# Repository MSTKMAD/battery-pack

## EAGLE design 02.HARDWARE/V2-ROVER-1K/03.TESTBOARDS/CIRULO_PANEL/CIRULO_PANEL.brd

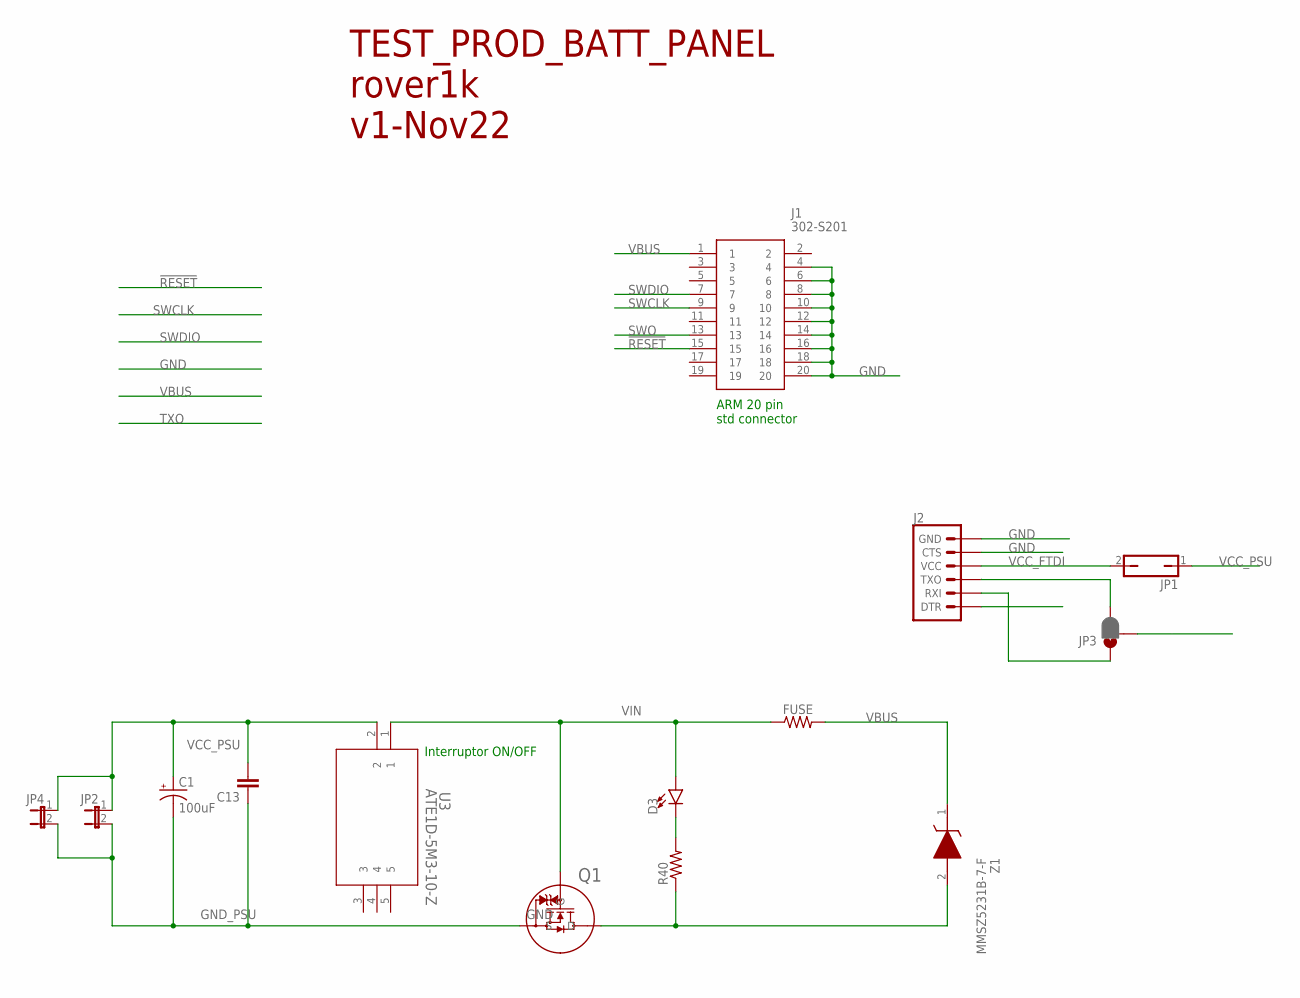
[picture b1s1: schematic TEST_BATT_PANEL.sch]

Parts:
C1: 100uF; CPOL-RADIAL-2.5MM-6.5MM
C13: C-EUC0805; C0805
D3: LED3MM; LED_3MM
FUSE: 0805
J1: 302-S201; SHDR20W66P254_2X10_3300X905X90
J2: 6_PIN_SERIAL_TARGET; 1X06
JP1: JP1Q; JP1
JP2, JP4: JP1E; JP1
JP3: JUMPER-SMT_3_1-NC_PASTE_NO-SILK; SMT-JUMPER_3_1-NC_PASTE_NO-SILK
Q1: PJA3416AE_R1_00001; SOT23_PJA3416_PNJ
R40: 10K; 0805
U3: ATE1D-5M3-10-Z; SPDT05_ATE1D_9P5X8_NDC
Z1: MMSZ5231B-7-F; SOD3716X145N

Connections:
!RESET: J1.15
GND: J1.4, J1.6, J1.8, J1.10, J1.12, J1.14, J1.16, J1.18, J1.20, J2.5 (CTS), J2.6 (GND), Q1.3 (D), R40.1, Z1.2 (A)
GND_PSU: C1.2 (-), C13.1, JP2.2, JP4.2, Q1.2 (S)
unnamed: D3.K (C), R40.2
RXI: J2.3 (TXO), JP3.3
SWCLK: J1.9
SWDIO: J1.7
SWO: J1.13
TXO: J2.2 (RXI), JP3.1
VBUS: FUSE.2, J1.1, Z1.1 (K)
VCC_FTDI: J2.4 (VCC), JP1.2
VCC_PSU: C1.1 (+), C13.2, JP1.1, JP2.1, JP4.1, U3.2
VIN: D3.A, FUSE.1, Q1.1 (G), U3.1

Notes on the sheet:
TEST_PROD_BATT_PANEL rover1k v1-Nov22
ARM 20 pin std connector
Interruptor ON/OFF

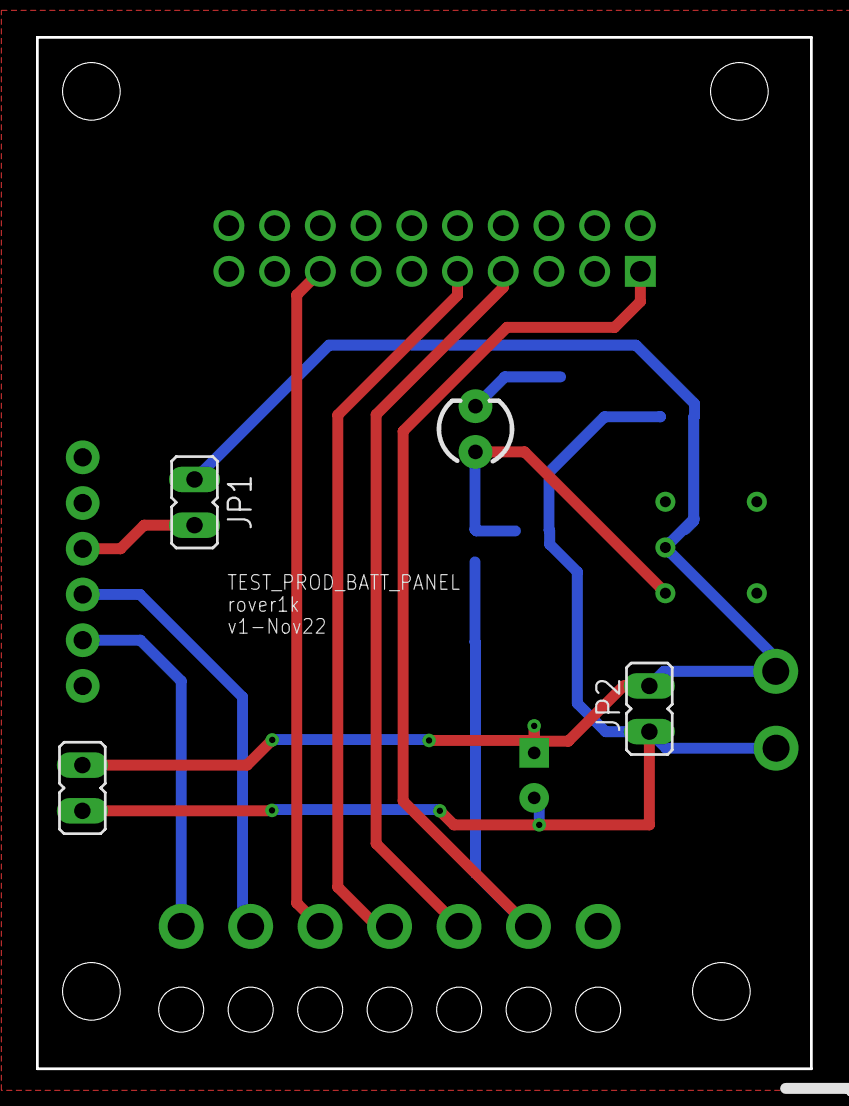
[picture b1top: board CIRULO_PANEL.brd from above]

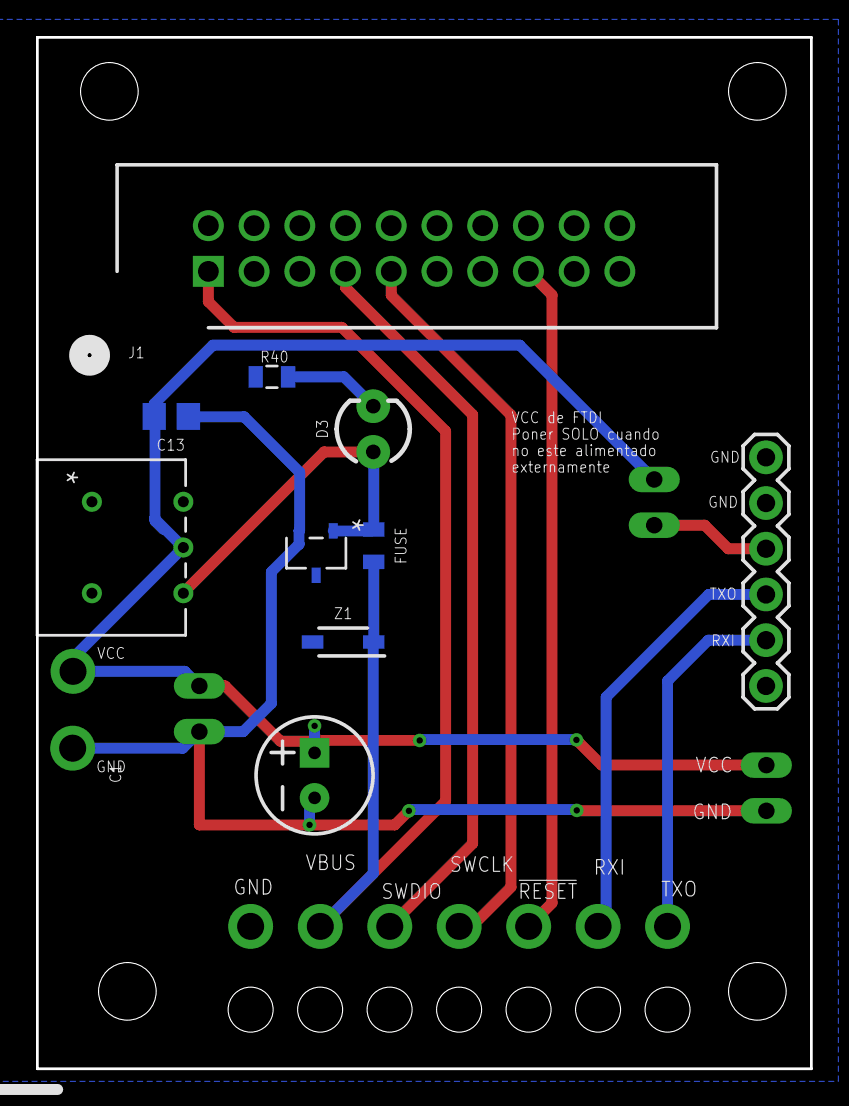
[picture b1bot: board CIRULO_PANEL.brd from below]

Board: 2 copper layers, 43.0 x 57.3 mm, 13 parts (10 on the bottom side), 7 nets.

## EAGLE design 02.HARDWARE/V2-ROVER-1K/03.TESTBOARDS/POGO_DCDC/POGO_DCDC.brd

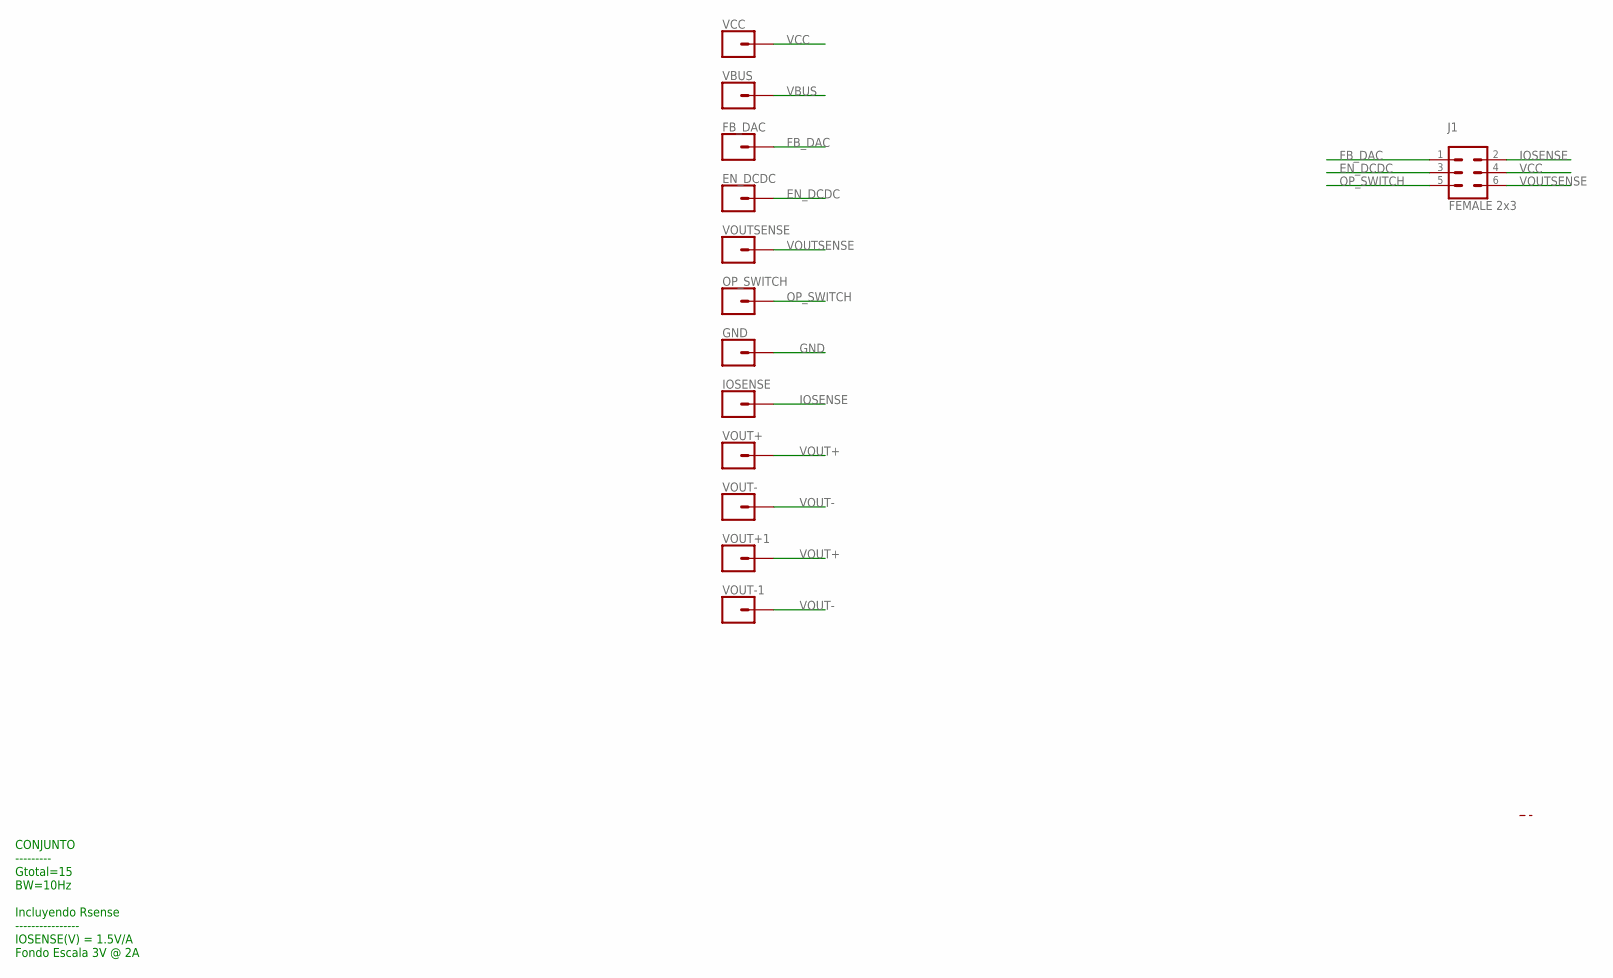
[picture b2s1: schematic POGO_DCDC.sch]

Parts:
EN_DCDC: CONN_01POGOPIN_HOLE_LARGE; 1X01_POGOPIN_HOLE_0.061_DIA
FB_DAC: CONN_01POGOPIN_HOLE_LARGE; 1X01_POGOPIN_HOLE_0.061_DIA
GND: CONN_01POGOPIN_HOLE_LARGE; 1X01_POGOPIN_HOLE_0.061_DIA
IOSENSE: CONN_01POGOPIN_HOLE_LARGE; 1X01_POGOPIN_HOLE_0.061_DIA
J1: FEMALE 2x3; 2X3
OP_SWITCH: CONN_01POGOPIN_HOLE_LARGE; 1X01_POGOPIN_HOLE_0.061_DIA
VBUS: CONN_01POGOPIN_HOLE_LARGE; 1X01_POGOPIN_HOLE_0.061_DIA
VCC: CONN_01POGOPIN_HOLE_LARGE; 1X01_POGOPIN_HOLE_0.061_DIA
VOUT+, VOUT+1: CONN_01POGOPIN_HOLE_LARGE; 1X01_POGOPIN_HOLE_0.061_DIA
VOUT-, VOUT-1: CONN_01POGOPIN_HOLE_LARGE; 1X01_POGOPIN_HOLE_0.061_DIA
VOUTSENSE: CONN_01POGOPIN_HOLE_LARGE; 1X01_POGOPIN_HOLE_0.061_DIA

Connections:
EN_DCDC: EN_DCDC.2, J1.3
FB_DAC: FB_DAC.2, J1.1
GND: GND.2
IOSENSE: IOSENSE.2, J1.2
OP_SWITCH: J1.5, OP_SWITCH.2
VBUS: VBUS.2
VCC: J1.4, VCC.2
VOUT+: VOUT+.2, VOUT+1.2
VOUT-: VOUT-.2, VOUT-1.2
VOUTSENSE: J1.6, VOUTSENSE.2

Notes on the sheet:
CONJUNTO --------- Gtotal=15 BW=10Hz Incluyendo Rsense ---------------- IOSENSE(V) = 1.5V/A Fondo Escala 3V @ 2A

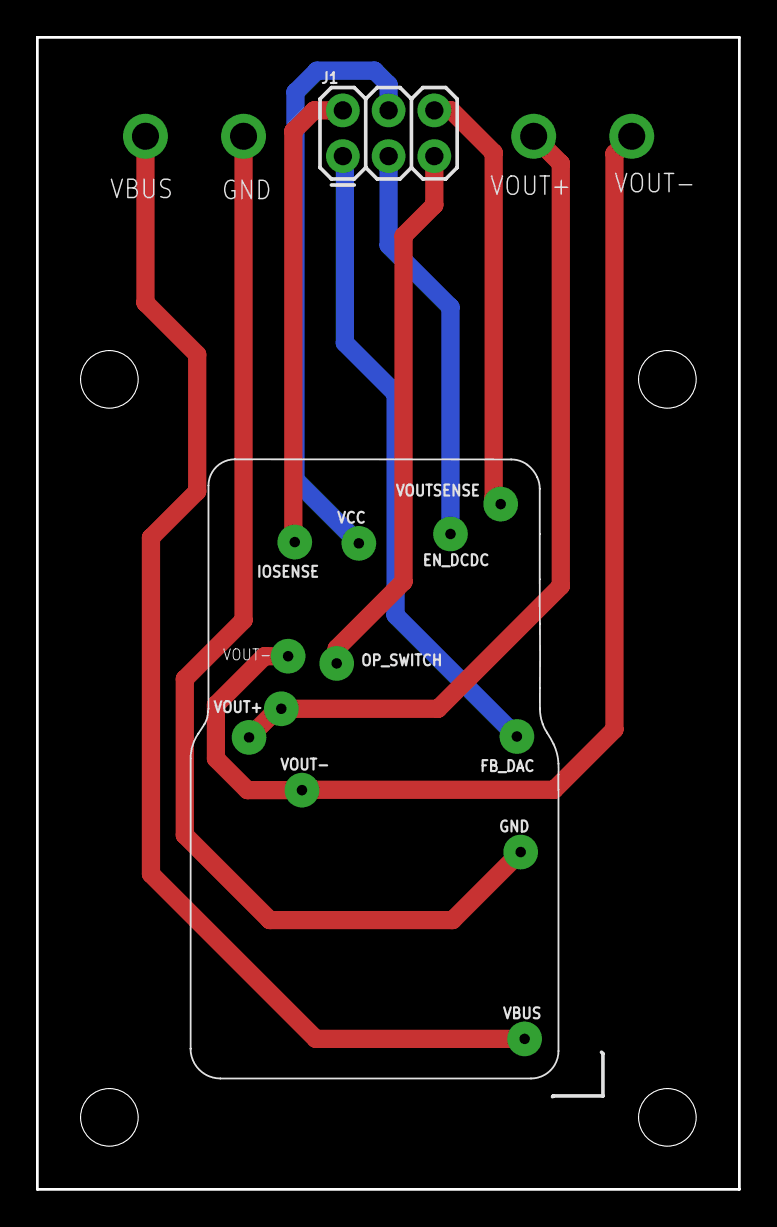
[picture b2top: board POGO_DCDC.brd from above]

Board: 2 copper layers, 39.0 x 64.0 mm, 13 parts (0 on the bottom side), 8 nets.

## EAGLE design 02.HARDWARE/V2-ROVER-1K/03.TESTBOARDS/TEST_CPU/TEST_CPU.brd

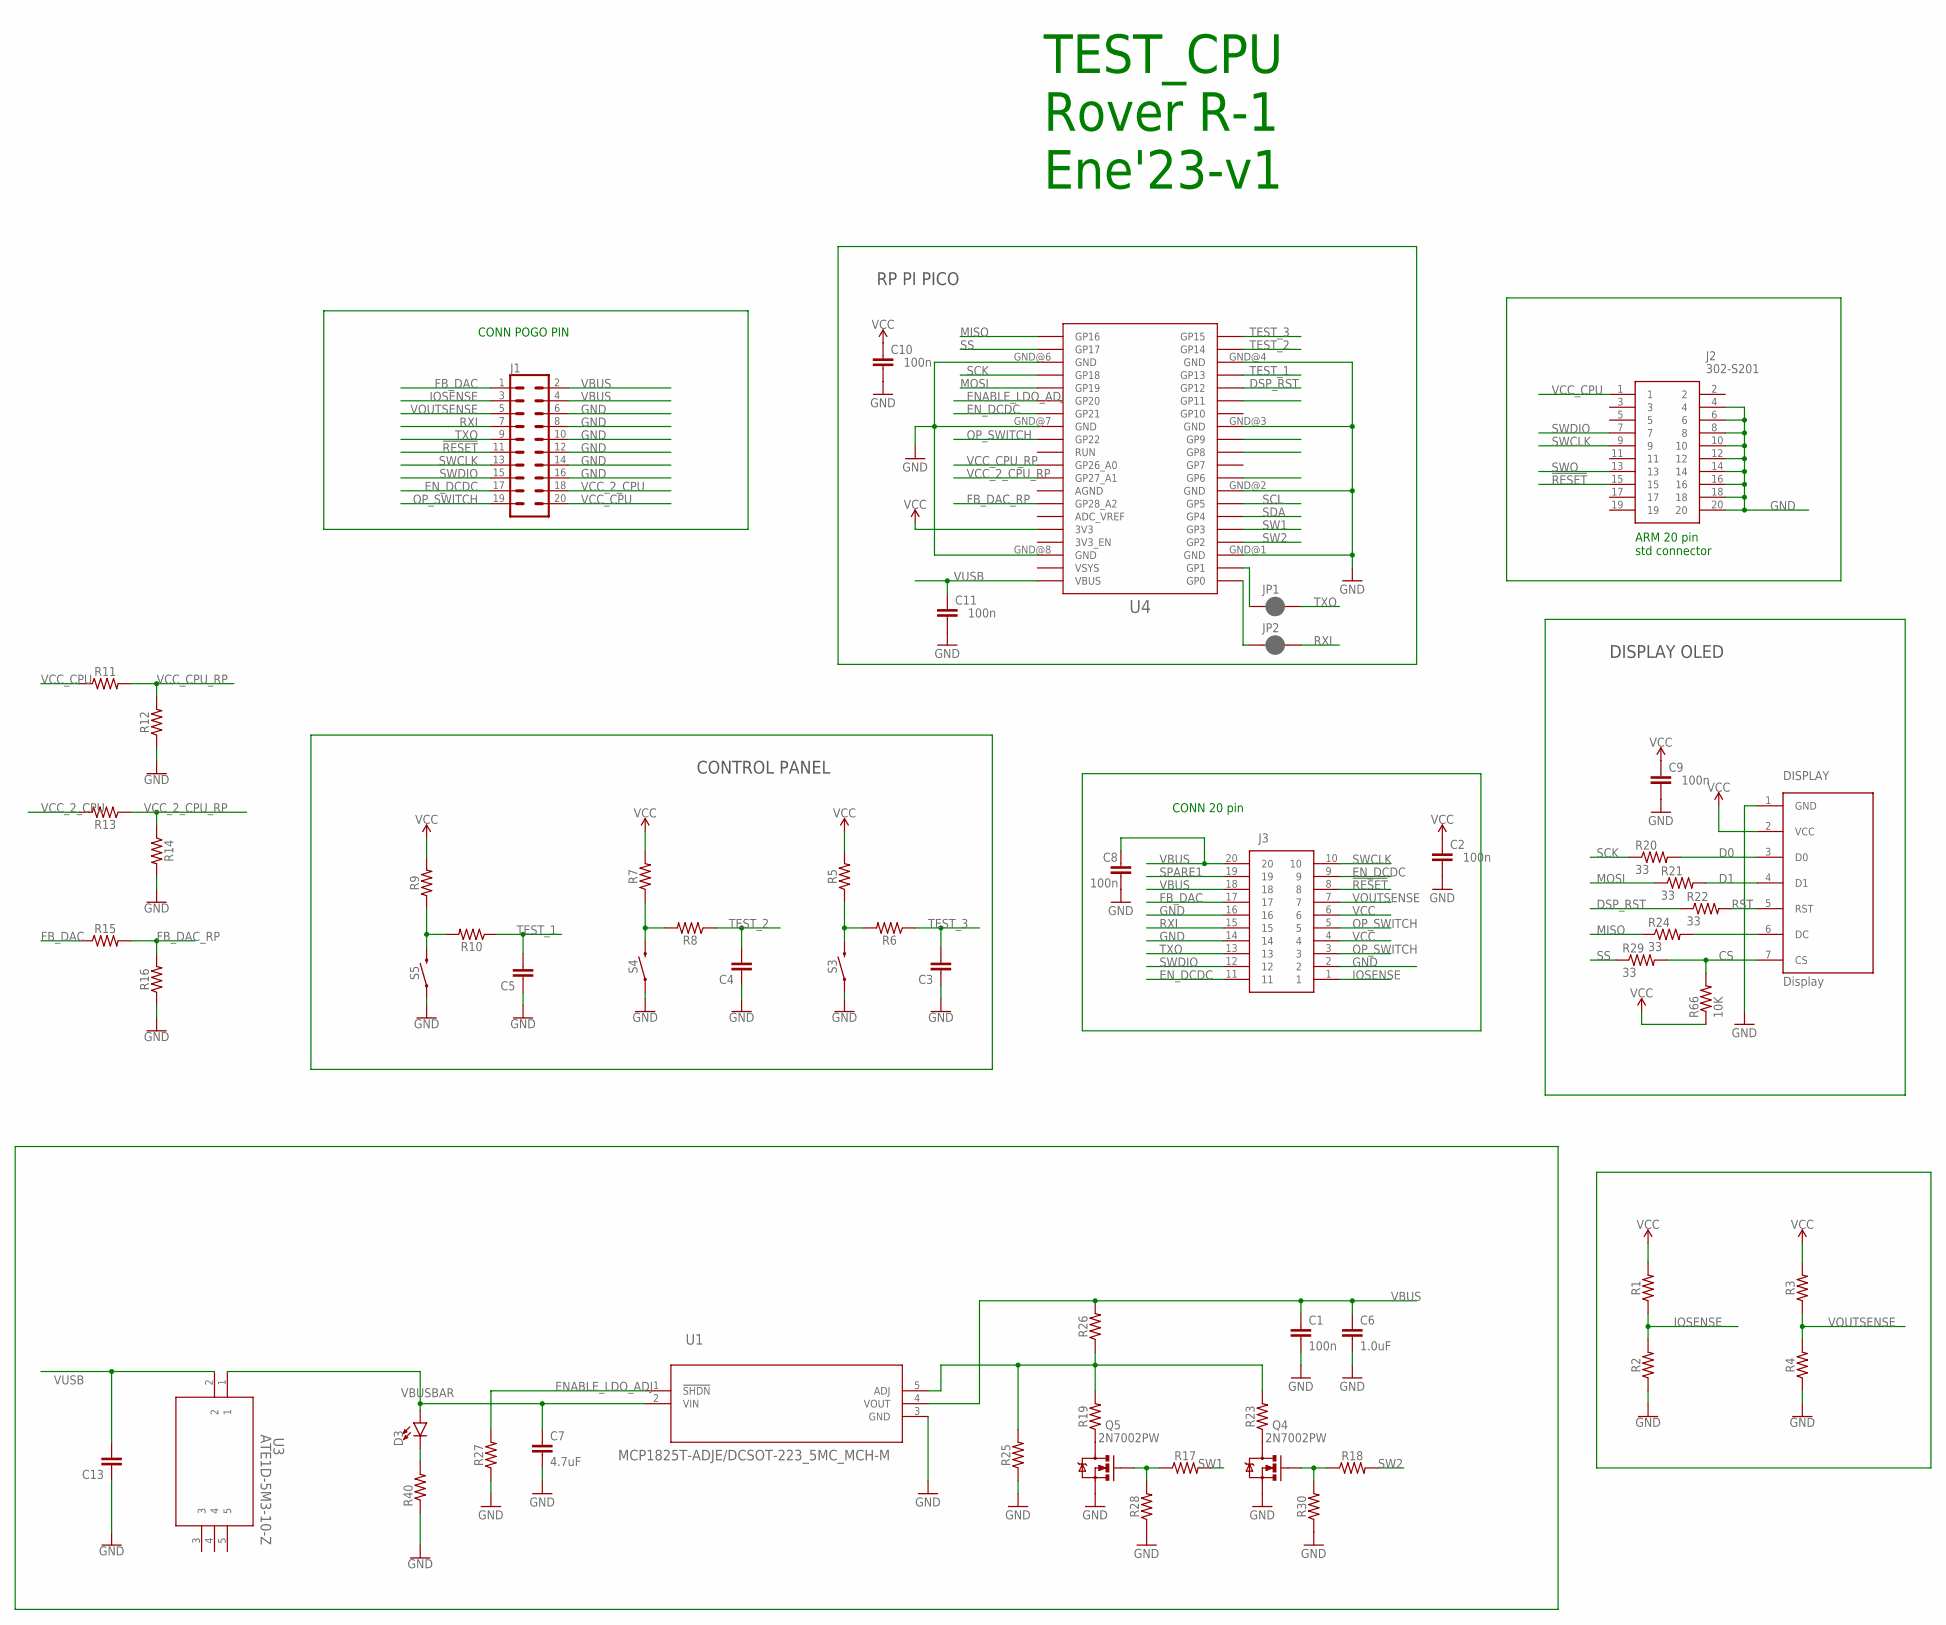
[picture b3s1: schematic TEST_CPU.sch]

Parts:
C1, C2, C8, C9, C10, C11: 100n; 0805
C3, C4, C5, C13: C-EUC0805; C0805
C6: 1.0uF; 0805
C7: 4.7uF; 0603
D3: LED3MM; LED_3MM
DISPLAY: Display; OLED_LCD
J1: CONN_10X2; 2X10
J2: 302-S201; SHDR20W66P254_2X10_3300X905X90
J3: DF40C-20DP-0.4V_51_; DF40C-20DPA
JP1, JP2: JUMPER-SMT_2_NC_PASTE_SILK; SMT-JUMPER_2_NC_PASTE_SILK
Q4, Q5: 2N7002PW; SOT323
R1, R2, R3, R4, R5, R6, R7, R8, R9, R10, R11, R12, R13, R14, R15, R16, R17, R18, R19, R23, R25, R26, R27, R28, R30: 0805
R20, R21, R22, R24, R29: 33; 0805
R40, R66: 10K; 0805
S3, S4, S5: MOMENTARY-SWITCH-SPST-SMD-5.2MM; TACTILE_SWITCH_SMD_5.2MM
U1: MCP1825T-ADJE/DCSOT-223_5MC_MCH-M; SOT-223_5MC_MCH-M
U3: ATE1D-5M3-10-Z; SPDT05_ATE1D_9P5X8_NDC
U4: RPI_PICO_IG-TH; RPI_PICO_TH

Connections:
!RESET: J1.11, J2.15, J3.8
CS: DISPLAY.7 (CS), R29.2, R66.2
D0: DISPLAY.3 (D0), R20.2
D1: DISPLAY.4 (D1), R21.2
DSP_RST: R22.1, U4.GP12
ENABLE_LDO_ADJ: R27.2, U1.1 (!SHDN), U4.GP20
EN_DCDC: J1.17, J3.9, J3.11, U4.GP21
FB_DAC: J1.1, J3.17, R15.1
FB_DAC_RP: R15.2, R16.2, U4.GP28_A2
GND: C1.2, C2.2, C3.1, C4.1, C5.1, C6.2, C7.2, C8.2, C9.2, C10.2, C11.2, C13.1, DISPLAY.1 (GND), J1.6, J1.8, J1.10, J1.12, J1.14, J1.16, J2.4, J2.6, J2.8, J2.10, J2.12, J2.14, J2.16, J2.18, J2.20, J3.2, J3.14, J3.16, Q4.2 (S), Q5.2 (S), R2.1, R4.1, R12.1, R14.2, R16.1, R25.1, R27.1, R28.1, R30.1, R40.1, S3.1, S4.1, S5.1, U1.3 (GND), U4.GND@1 (GND), U4.GND@2 (GND), U4.GND@3 (GND), U4.GND@4 (GND), U4.GND@6 (GND), U4.GND@7 (GND), U4.GND@8 (GND)
IOSENSE: J1.3, J3.1, R1.1, R2.2
MISO: R24.1, U4.GP16
MOSI: R21.1, U4.GP19
unnamed: R5.1, R6.2, S3.3 (2)
unnamed: R7.1, R8.2, S4.3 (2)
unnamed: JP1.1, U4.GP1
unnamed: R9.1, R10.2, S5.3 (2)
unnamed: JP2.1, U4.GP0
unnamed: DISPLAY.6 (DC), R24.2
unnamed: R19.2, R23.2, R25.2, R26.1, U1.5 (ADJ)
unnamed: Q5.1 (G), R17.1, R28.2
unnamed: D3.K (C), R40.2
unnamed: Q5.3 (D), R19.1
unnamed: Q4.1 (G), R18.1, R30.2
unnamed: Q4.3 (D), R23.1
OP_SWITCH: J1.19, J3.3, J3.5, U4.GP22
RST: DISPLAY.5 (RST), R22.2
RXI: J1.7, J3.15, JP2.2
SCK: R20.1, U4.GP18
SCL: U4.GP5
SDA: U4.GP4
SPARE1: J3.19
SS: R29.1, U4.GP17
SW1: R17.2, U4.GP3
SW2: R18.2, U4.GP2
SWCLK: J1.13, J2.9, J3.10
SWDIO: J1.15, J2.7, J3.12
SWO: J2.13
TEST_1: C5.2, R10.1, U4.GP13
TEST_2: C4.2, R8.1, U4.GP14
TEST_3: C3.2, R6.1, U4.GP15
TXO: J1.9, J3.13, JP1.2
VBUS: C1.1, C6.1, C8.1, J1.2, J1.4, J3.18, J3.20, R26.2, U1.4 (VOUT)
VBUSBAR: C7.1, D3.A, U1.2 (VIN), U3.1
VCC: C2.1, C9.1, C10.1, DISPLAY.2 (VCC), J3.4, J3.6, R1.2, R3.2, R5.2, R7.2, R9.2, R66.1, U4.3V3
VCC_2_CPU: J1.18, R13.2
VCC_2_CPU_RP: R13.1, R14.1, U4.GP27_A1
VCC_CPU: J1.20, J2.1, R11.1
VCC_CPU_RP: R11.2, R12.2, U4.GP26_A0
VOUTSENSE: J1.5, J3.7, R3.1, R4.2
VUSB: C11.1, C13.2, U3.2, U4.VBUS

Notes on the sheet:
TEST_CPU Rover R-1 Ene'23-v1
CONTROL PANEL
DISPLAY OLED
RP PI PICO
ARM 20 pin std connector
CONN 20 pin
CONN POGO PIN

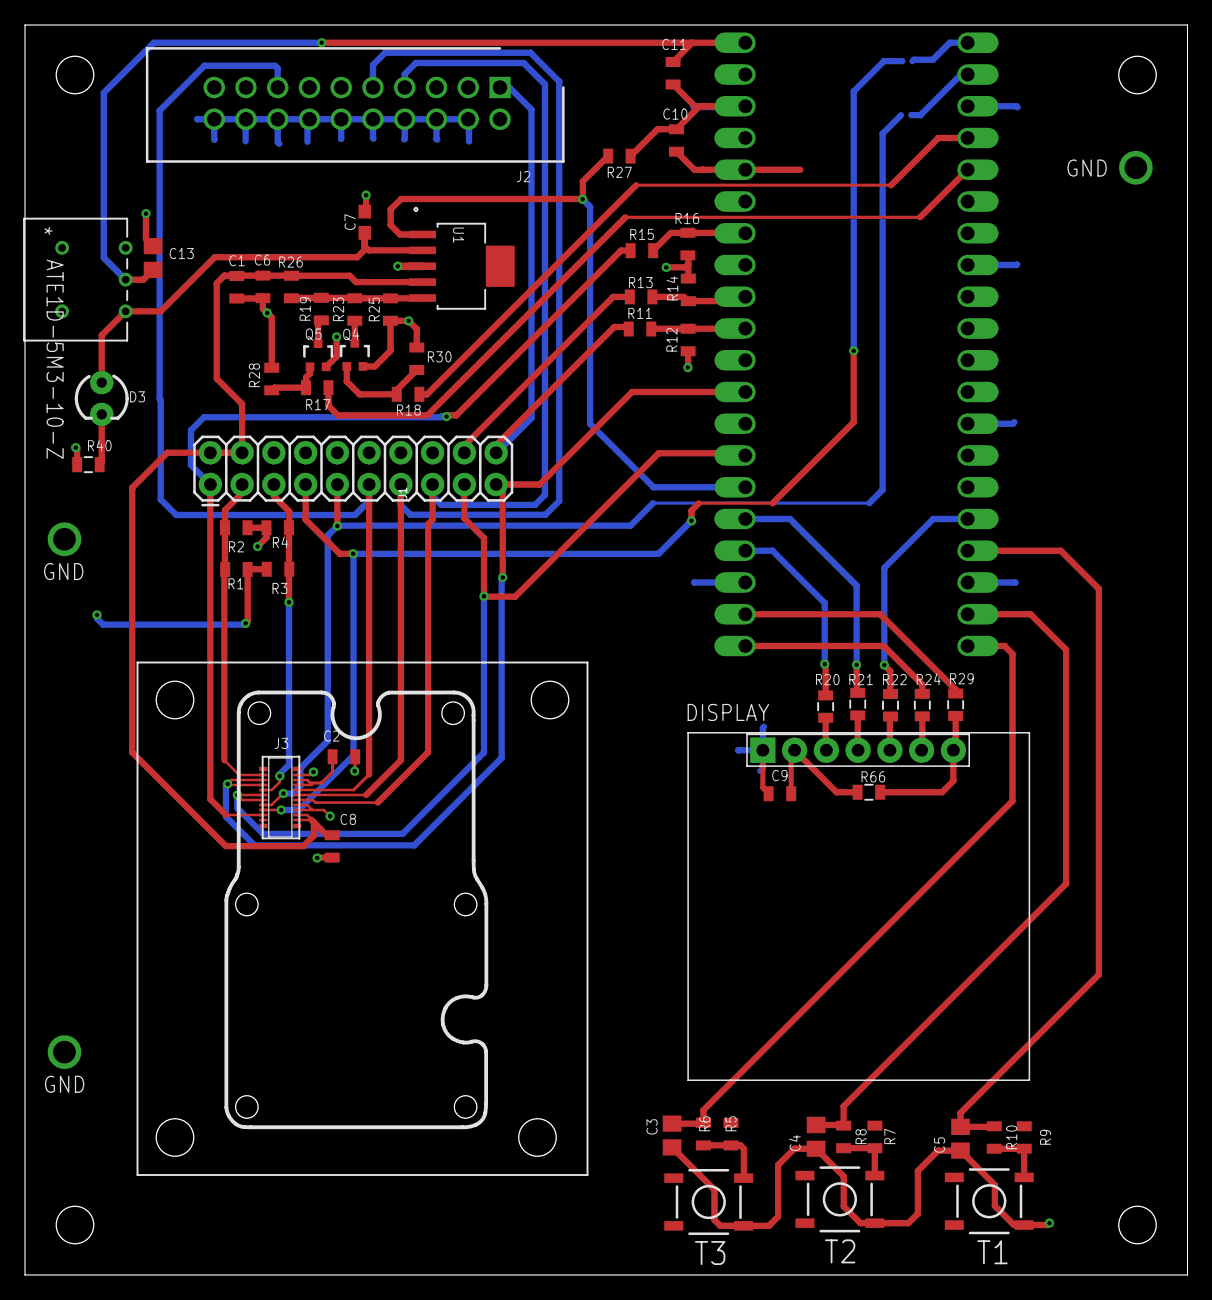
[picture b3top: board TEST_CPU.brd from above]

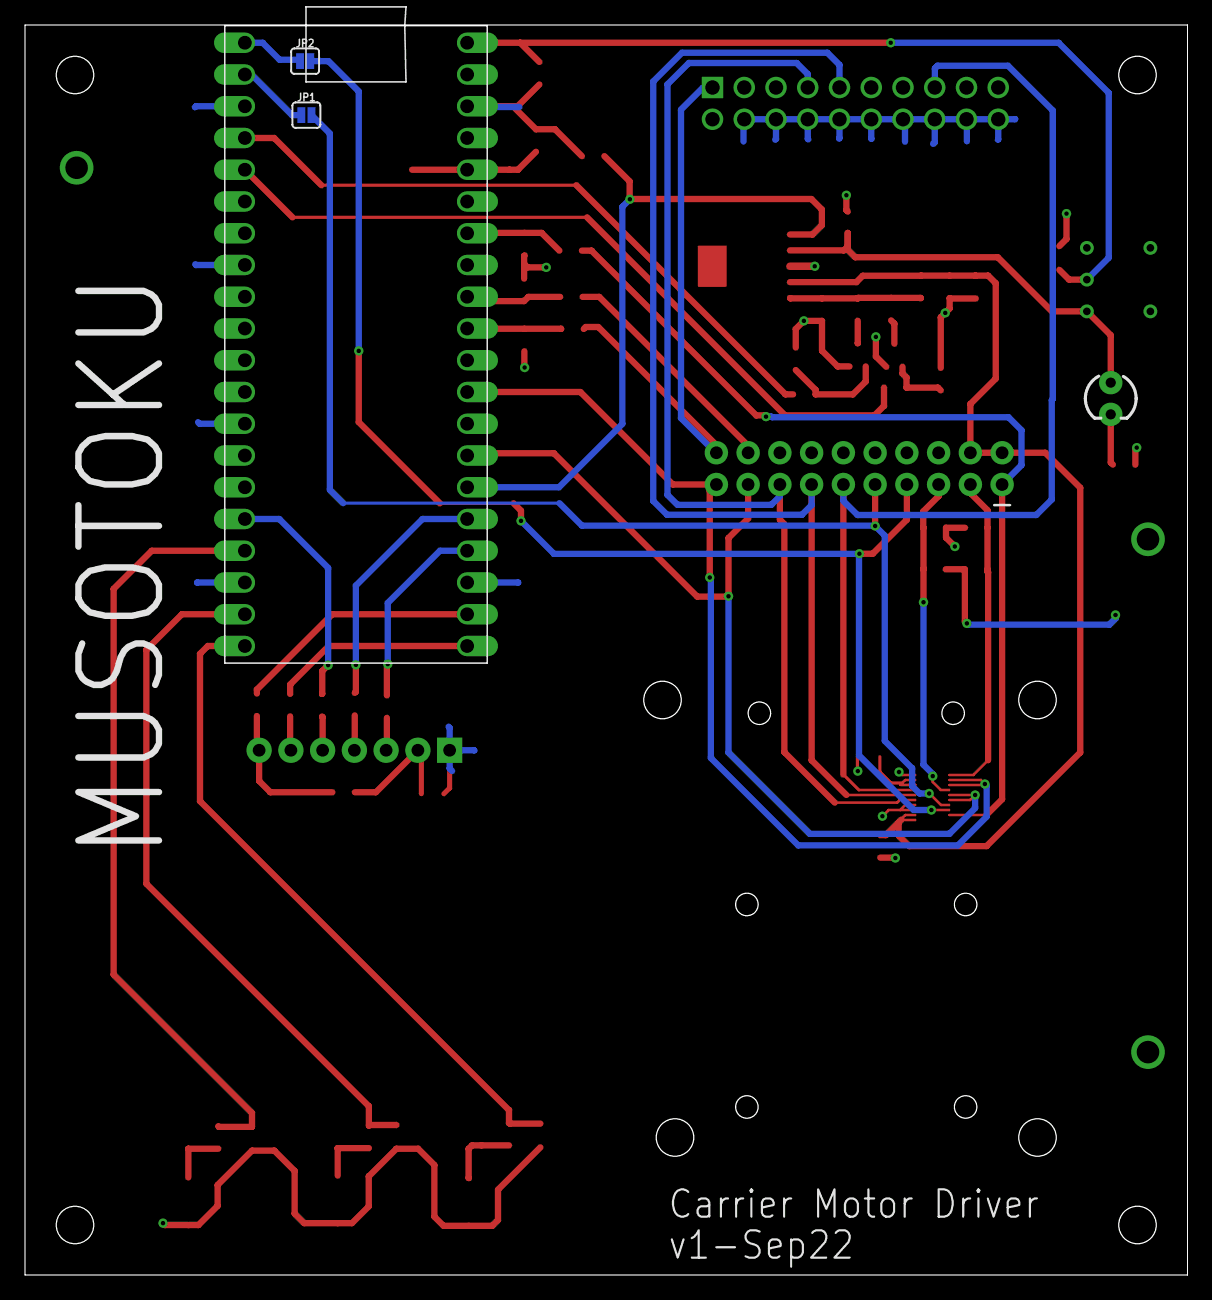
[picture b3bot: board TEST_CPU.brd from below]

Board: 2 copper layers, 93.0 x 100.0 mm, 59 parts (3 on the bottom side), 47 nets.

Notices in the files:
parts and their libraries:
SparkFun-LED: Licensing: Creative Commons ShareAlike 4.0 International - https://creativecommons.org/licenses/by-sa/4.0
COPYRIGHT: Copyright (C) 2022 Ultra Librarian. All rights reserved.
